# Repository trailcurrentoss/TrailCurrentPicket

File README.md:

# TrailCurrent Picket

Sensor module that monitors cabinet and door open/closed states using reed switches and reports status over a CAN bus interface. Part of the [TrailCurrent](https://trailcurrent.com) open-source vehicle platform.

## Hardware Overview

- **Board:** [Waveshare ESP32-S3-RS485-CAN](https://www.waveshare.com/esp32-s3-rs485-can.htm)
- **Microcontroller:** ESP32-S3
- **Framework:** ESP-IDF
- **Function:** Cabinet and door state monitoring with CAN bus reporting
- **Key Features:**
  - 13 reed switch inputs for open/closed detection
  - CAN bus communication at 500 kbps (onboard TJA1051 transceiver)
  - Firmware-configurable CAN address via NVS (up to 8 modules per bus)
  - Over-the-air (OTA) firmware updates via WiFi (triggered over CAN)
  - Onboard status LED
  - Custom flash partition layout with dual OTA slots

### Design Specifications

- **Operating Temperature:** -20°C to +70°C
- **Power:** 7-36V DC input via onboard buck converter
- **Data Rate:** 5 transmissions per second

## CAN Bus Addressing

The CAN message ID is set at compile time via the `PICKET_ADDRESS` build flag. Valid values are **0 through 7**, giving 8 possible modules on the same bus. The CAN ID is computed as `0x0A + PICKET_ADDRESS`. Default is 0 if not specified. The build will fail if a value outside 0-7 is used.

```bash
# Build with default address 0 (CAN ID 0x0A)
idf.py build

# Build for address 3 (CAN ID 0x0D)
idf.py build -DPICKET_ADDRESS=3
```

| `PICKET_ADDRESS` | CAN ID | DBC Message Name     |
|-------------------|--------|----------------------|
| 0 (default)       | 0x0A   | PicketStatus0        |
| 1                 | 0x0B   | PicketStatus1        |
| 2                 | 0x0C   | PicketStatus2        |
| 3                 | 0x0D   | PicketStatus3        |
| 4                 | 0x0E   | PicketStatus4        |
| 5                 | 0x0F   | PicketStatus5        |
| 6                 | 0x10   | PicketStatus6        |
| 7                 | 0x11   | PicketStatus7        |

#### Building All Variants

Use `build-all.sh` to build all 8 address variants in a single run:

```bash
./build-all.sh
```

This produces:

```
build/picket_addr0.bin   # Address 0 (CAN ID 0x0A)
build/picket_addr1.bin   # Address 1 (CAN ID 0x0B)
...
build/picket_addr7.bin   # Address 7 (CAN ID 0x11)
```

#### Creating a GitHub Release

After building all variants, upload all 8 binaries as release assets:

```bash
git tag -a v1.0.0 -m "Firmware release v1.0.0"
git push origin v1.0.0

gh release create v1.0.0 \
  build/picket_addr0.bin \
  build/picket_addr1.bin \
  build/picket_addr2.bin \
  build/picket_addr3.bin \
  build/picket_addr4.bin \
  build/picket_addr5.bin \
  build/picket_addr6.bin \
  build/picket_addr7.bin \
  --repo trailcurrentoss/TrailCurrentPicket \
  --title "v1.0.0" \
  --notes "Firmware release v1.0.0"
```

The Headwaters deployment system and the web-based firmware installer both expect these 8 files per release. The naming convention `{type}_addr{N}.bin` is required.

### CAN Message Format

Each module transmits a 2-byte message at 5 Hz (200 ms interval):

| Byte | Bits  | Description                          |
|------|-------|--------------------------------------|
| 0    | 0-7   | Door status 1-8 (RSW01-RSW08)       |
| 1    | 0-4   | Door status 9-13 (RSW09-RSW13)      |
| 1    | 5-7   | Reserved                             |

Each bit represents one reed switch: `1` = door open, `0` = door closed.

### CAN Control Messages

The module also listens for control messages from other nodes:

- **CAN ID 0x00 - OTA Update Notification:** Contains a 3-byte MAC address suffix. If it matches this module's hostname, the module connects to WiFi using stored credentials and enters OTA update mode.
- **CAN ID 0x01 - WiFi Credential Configuration:** Multi-message protocol to receive and store WiFi SSID and password in NVS flash for future OTA updates.
- **CAN ID 0x02 - Discovery Trigger:** Broadcast with no payload. Unconfigured modules respond by joining WiFi and advertising via mDNS for Headwaters to discover and register them.
- **CAN ID 0x03 - Discovery Reset:** Targeted by MAC address. Clears the configured flag so the module responds to the next discovery trigger.
- **CAN ID 0x04 - Firmware Version Report:** Sent once on boot. Payload: `[mac3, mac4, mac5, major, minor, patch]`. Reports running firmware version to Headwaters.

### Module Discovery

New modules are automatically discovered by Headwaters using a one-at-a-time registration protocol:

1. Headwaters sends CAN ID 0x02 (broadcast, no payload)
2. Unconfigured modules join WiFi and advertise `_trailcurrent._tcp` via mDNS with TXT records: `type`, `addr`, `canid`, `fw`
3. Headwaters browses mDNS, reads the metadata, and sends `GET /discovery/confirm`
4. Module marks itself configured in NVS and tears down WiFi

The discovery window is 30 seconds. The status LED blinks at 4 Hz during discovery. Already-configured modules ignore the trigger. To re-discover a module, send CAN ID 0x03 with its MAC bytes to clear the configured flag.

### Firmware Version

The firmware version is set in `CMakeLists.txt` via `PROJECT_VER` and reported during discovery via the `fw` mDNS TXT record. It is also available at runtime via `esp_app_get_description()`.

## GPIO Pin Assignments

### Onboard (not on pin header)

| GPIO | Function       | Notes                                |
|------|---------------|--------------------------------------|
| 0    | Status LED    | Onboard LED                          |
| 15   | CAN TX        | Onboard TJA1051 transceiver          |
| 16   | CAN RX        | Onboard TJA1051 transceiver          |
| 19   | USB D_N       | USB Serial/JTAG (flash + monitor)    |
| 20   | USB D_P       | USB Serial/JTAG (flash + monitor)    |

### Pin Header (reed switch inputs)

| GPIO | Function | Notes                            |
|------|----------|----------------------------------|
| 4    | RSW01    | Internal pull-up, no ext. resistor |
| 5    | RSW02    | Internal pull-up, no ext. resistor |
| 6    | RSW03    | Internal pull-up, no ext. resistor |
| 7    | RSW04    | Internal pull-up, no ext. resistor |
| 8    | RSW05    | Internal pull-up, no ext. resistor |
| 9    | RSW06    | Internal pull-up, no ext. resistor |
| 10   | RSW07    | Internal pull-up, no ext. resistor |
| 11   | RSW08    | Internal pull-up, no ext. resistor |
| 12   | RSW09    | Internal pull-up, no ext. resistor |
| 13   | RSW10    | Internal pull-up, no ext. resistor |
| 14   | RSW11    | Internal pull-up, no ext. resistor |
| 43   | RSW12    | Internal pull-up, no ext. resistor |
| 44   | RSW13    | Internal pull-up, no ext. resistor |

## Hardware Requirements

### Components

- **Board:** [Waveshare ESP32-S3-RS485-CAN](https://www.waveshare.com/esp32-s3-rs485-can.htm) — industrial-grade board with onboard CAN transceiver, buck converter (7-36V input), and pin header for sensor connections
- **Sensors:** Normally Open (NO) reed switches
- **Connectors:** Wire to pin header (2x10, 2.54mm pitch)

### KiCAD Library Dependencies

This project uses the consolidated [TrailCurrentKiCADLibraries](https://github.com/trailcurrentoss/TrailCurrentKiCADLibraries).

**Setup:**

```bash
# Clone the library alongside this project
git clone git@github.com:trailcurrentoss/TrailCurrentKiCADLibraries.git

# Set environment variables (add to ~/.bashrc or ~/.zshrc)
# Adjust paths to where you cloned the library
export TRAILCURRENT_SYMBOL_DIR="../TrailCurrentKiCADLibraries/symbols"
export TRAILCURRENT_FOOTPRINT_DIR="../TrailCurrentKiCADLibraries/footprints"
export TRAILCURRENT_3DMODEL_DIR="../TrailCurrentKiCADLibraries/3d_models"
```

See [KICAD_ENVIRONMENT_SETUP.md](https://github.com/trailcurrentoss/TrailCurrentKiCADLibraries/blob/main/KICAD_ENVIRONMENT_SETUP.md) in the library repository for detailed setup instructions.

## Firmware

The firmware is built with ESP-IDF (not PlatformIO/Arduino).

### Build & Flash

```bash
# Source ESP-IDF environment
source ~/esp/v5.5.2/esp-idf/export.sh

# Set target (first time only)
idf.py set-target esp32s3

# Build (default address 0, CAN ID 0x0A)
idf.py build

# Build with a specific module address (0-7)
idf.py build -DPICKET_ADDRESS=3

# Flash via USB
idf.py -p /dev/ttyACM0 flash

# Monitor serial output
idf.py -p /dev/ttyACM0 monitor
```

### OTA Update

```bash
# Use the binary matching the module's address
curl -X POST http://esp32-XXYYZZ.local/ota --data-binary @build/picket_addr0.bin
```

Where `XXYYZZ` is the last 3 bytes of the device's WiFi MAC address (printed at boot).

## Opening the Project

1. **Set up environment variables** (see Library Dependencies above)
2. **Open KiCAD:**
   ```bash
   kicad EDA/TrailCurrentPicketModule/TrailCurrentPicketModule.kicad_pro
   ```
3. **Verify libraries load** - All symbol and footprint libraries should resolve without errors
4. **View 3D models** - Open PCB and press `Alt+3` to view the 3D visualization

## Manufacturing

- **PCB Files:** Ready for fabrication via standard PCB services (JLCPCB, OSH Park, etc.)
- **BOM Generation:** Export BOM from KiCAD schematic (Tools > Generate BOM)
- **Enclosure:** FreeCAD design included in `CAD/` directory
- **JLCPCB Assembly:** See [BOM_ASSEMBLY_WORKFLOW.md](https://github.com/trailcurrentoss/TrailCurrentKiCADLibraries/blob/main/BOM_ASSEMBLY_WORKFLOW.md) for detailed assembly workflow

## Documentation

- **Requirements:** See `DOCS/Requirements/high-level-requirements.md` for detailed specifications

## Project Structure

```
├── CAD/                          # FreeCAD enclosure design
├── DOCS/                         # Requirements documentation
│   └── Requirements/
│       └── high-level-requirements.md
├── EDA/                          # KiCAD hardware design files
│   └── TrailCurrentPicketModule/
│       ├── *.kicad_pro           # KiCAD project
│       ├── *.kicad_sch           # Schematic
│       └── *.kicad_pcb           # PCB layout
├── main/                         # ESP-IDF firmware source
│   ├── main.c                    # Main application, CAN task, reed switch reading
│   ├── discovery.h / discovery.c # mDNS self-discovery and Headwaters registration
│   ├── ota.h / ota.c             # OTA firmware updates via WiFi
│   ├── wifi_config.h / .c        # WiFi credential storage and CAN provisioning
│   ├── CMakeLists.txt            # Component build config
│   └── idf_component.yml         # Component dependencies
├── CMakeLists.txt                # ESP-IDF project root
├── partitions.csv                # Flash partition layout
├── build-all.sh                  # Build all 8 address variants (addr 0-7)
└── sdkconfig.defaults            # Default build configuration
```

## License

MIT License - See LICENSE file for details.

This is open source hardware. You are free to use, modify, and distribute these designs for personal or commercial purposes.

## Contributing

Improvements and contributions are welcome! Please submit issues or pull requests.

## Support

For questions about:
- **KiCAD setup:** See [KICAD_ENVIRONMENT_SETUP.md](https://github.com/trailcurrentoss/TrailCurrentKiCADLibraries/blob/main/KICAD_ENVIRONMENT_SETUP.md)
- **Assembly workflow:** See [BOM_ASSEMBLY_WORKFLOW.md](https://github.com/trailcurrentoss/TrailCurrentKiCADLibraries/blob/main/BOM_ASSEMBLY_WORKFLOW.md)

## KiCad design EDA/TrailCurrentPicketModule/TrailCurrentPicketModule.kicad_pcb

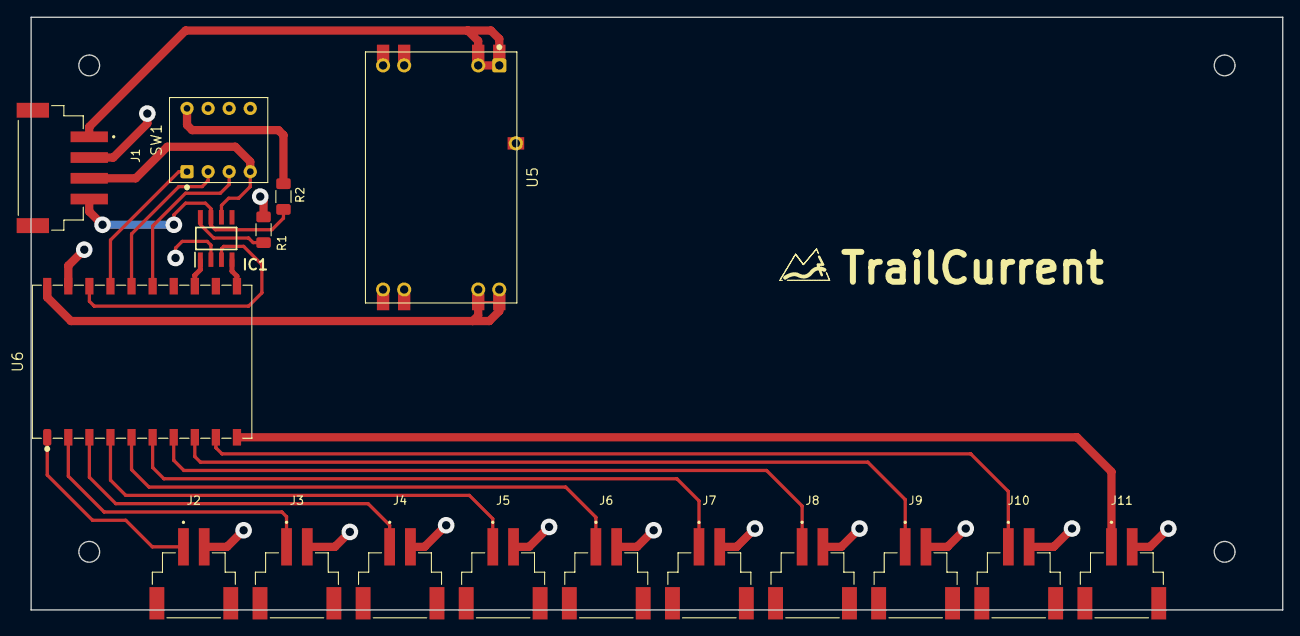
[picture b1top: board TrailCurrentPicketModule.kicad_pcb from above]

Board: 2 copper layers, 150.8 x 71.4 mm, 19 parts (0 on the bottom side), 23 nets.

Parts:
IC1: SN65HVD230DR
J1: S4B-XH-SM4-TB; JST_S4B-XH-SM4-TB
J2, J3, J4, J5, J6, J7, J8, J9, J10, J11: S2B-XH-SM4-TB; JST_S2B-XH-SM4-TB
LOGO: TrailCurrentLogo_Text
LOGO#2: TrailCurrentLogo_Icon
R1: 10k; R_1206_3216Metric_Pad1.30x1.75mm_HandSolder
R2: 120; R_1206_3216Metric_Pad1.30x1.75mm_HandSolder
SW1: DS-04
U5: Mini560
U6: ESP32-C6-SuperMini; ESP32-C6-SuperMini_SMD

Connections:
+3.3V: IC1.3 (VCC), U6.13 (3V3)
+5V: U5.8 (VOUT+), U5.9 (VOUT+), U6.11 (5V)
+12V: J1.1, U5.1 (VIN+), U5.2 (VIN+)
ADDR01: SW1.3, U6.16 (GPIO18)
ADDR02: SW1.2, U6.15 (GPIO19)
ADDR03: SW1.1, U6.14 (GPIO20)
CANH: IC1.7 (CANH), J1.4, R2.1
CANL: IC1.6 (CANL), J1.3, SW1.4
CAN_RX: IC1.4 (R), U6.20 (GPIO8)
CAN_TX: IC1.1 (D), U6.18 (GPIO14)
GND: IC1.2 (GND), J1.2, J2.2, J3.2, J4.2, J5.2, J6.2, J7.2, J8.2, J9.2, J10.2, J11.2, R1.1, SW1.5, SW1.6, SW1.7, U5.3 (GND), U5.4 (GND), U5.6 (GND), U5.7 (GND), U6.12 (GND)
unnamed: IC1.8 (RS), R1.2
unnamed: R2.2, SW1.8
RSW01: J2.1, U6.1 (TX)
RSW02: J3.1, U6.2 (RX)
RSW03: J4.1, U6.3 (GPIO0)
RSW04: J5.1, U6.4 (GPIO1)
RSW05: J6.1, U6.5 (GPIO2)
RSW06: J7.1, U6.6 (GPIO3)
RSW07: J8.1, U6.7 (GPIO4)
RSW08: J9.1, U6.8 (GPIO5)
RSW09: J10.1, U6.9 (GPIO6)
RSW10: J11.1, U6.10 (GPIO7)

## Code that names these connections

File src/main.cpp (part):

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// Reed switch inputs (Normally Open - close when magnet nearby / door closed)
// HIGH = door open, LOW = door closed (using internal pull-ups)
static const gpio_num_t RSW_PINS[] = {
  GPIO_NUM_16,  // RSW01 (TX pin - free since USB CDC is used for Serial)
  GPIO_NUM_17,  // RSW02 (RX pin - free since USB CDC is used for Serial)
  GPIO_NUM_0,   // RSW03
  GPIO_NUM_1,   // RSW04
  GPIO_NUM_2,   // RSW05
  GPIO_NUM_3,   // RSW06
  GPIO_NUM_4,   // RSW07
  GPIO_NUM_5,   // RSW08
  GPIO_NUM_6,   // RSW09
  GPIO_NUM_7,   // RSW10
};
static const uint8_t NUM_RSW = sizeof(RSW_PINS) / sizeof(RSW_PINS[0]);

// DIP switch address pins (active LOW - switches pull to GND when ON)
static const gpio_num_t ADDR_PINS[] = {
  GPIO_NUM_18,  // ADDR01 (bit 0 - LSB)
  GPIO_NUM_19,  // ADDR02 (bit 1)
  GPIO_NUM_20,  // ADDR03 (bit 2 - MSB)
};
static const uint8_t NUM_ADDR_PINS = sizeof(ADDR_PINS) / sizeof(ADDR_PINS[0]);

// CAN bus pins
static const gpio_num_t CAN_TX_PIN = GPIO_NUM_14;
static const gpio_num_t CAN_RX_PIN = GPIO_NUM_15;

// RGB LED (built-in WS2812 on GPIO8)
static const uint8_t RGB_LED_PIN = 8;

// =============================================================================
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  debugln("[INIT] Picket starting");
#endif

  // Initialize RGB LED (built-in WS2812 on GPIO8)
  statusLed.begin();
  statusLed.setBrightnessPercent(1);

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  // Initialize CAN bus
  TwaiTaskBased::onReceive(onCanRx);
  TwaiTaskBased::onTransmit(onCanTx);
  TwaiTaskBased::begin(CAN_TX_PIN, CAN_RX_PIN, CAN_BAUDRATE, TWAI_MODE_NO_ACK);
  debugln("[INIT] TWAI started on GPIO14 (TX) / GPIO15 (RX)");

  // Read initial state
  debouncedState = readReedSwitches();
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
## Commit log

2026-03-02 Switching to waveshare ESP32-C6 module given better documentation over previously purchased modules
2026-03-08 Renamed to align with product names
2026-03-26 Updates to fix the CAN controller to have NO ACK
2026-03-26 Moving to ESP-IDF
2026-03-26 Dependencies updated
2026-03-26 Self discovery added
2026-03-26 Improved CAN handling so nodes can enter and leave the network as well as be on the network alone and auto recover
2026-03-27 Fixes to get discovery working from headwaters
2026-03-27 Additional changes for discovery fixes
2026-03-28 Fixed bug where discovery would disrupt CAN messaging
2026-03-28 OTA and discovery algned with other projects
2026-03-28 Fixing issue with CAN Bus stops responding when discovery happens
2026-03-29 Changes to provide version on OTA
2026-04-12 Adding discovery for this device
